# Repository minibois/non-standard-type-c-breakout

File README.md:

# mini-type-c-breakout
## Repository for a simple USB Type C breakout board, where the receptacle installs on the other side
 << [License](https://github.com/minibois/mini-non-standard-type-c-breakout/blob/master/LICENSE/LICENSE.txt) || [Bill of Materials](https://github.com/minibois/non-standard-type-c-breakout/blob/master/Documents/BOM.txt) || Schematic ([.pdf](https://github.com/minibois/mini-non-standard-type-c-breakout/blob/master/Documents/Schematic.pdf)) / ([.sch](https://github.com/minibois/mini-non-standard-type-c-breakout/blob/master/mini-type-c-breakout.sch)) || PCB ([.pdf](https://github.com/minibois/mini-non-standard-type-c-breakout/blob/master/Documents/PCB.pdf)) / ([.kicad_pcb](https://github.com/minibois/mini-non-standard-type-c-breakout/blob/master/mini-type-c-breakout.kicad_pcb)) >>

 This daughterboard allows for a USB 2.0 Type C by HRO receptacle to be installed on the opposite side of the Type C pins. This daughterboard was used in a keyboard repair project, so the receptacle could be installed on the keyboard cleanly.

### This PCB file and schematic is provided - as per CERN-OHL-S v2 section 6 - _without any warranty_ (implied or otherwise). https://ohwr.org/cern_ohl_s_v2.pdf

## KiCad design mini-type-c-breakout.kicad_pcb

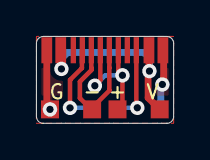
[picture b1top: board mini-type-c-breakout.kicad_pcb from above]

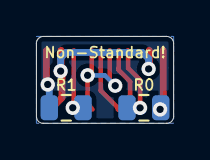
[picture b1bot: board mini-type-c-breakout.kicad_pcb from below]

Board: 2 copper layers, 7.6 x 4.8 mm, 7 parts (2 on the bottom side), 6 nets.

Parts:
+: Conn_01x01; TestPoint_Pad_1.0x1.0mm
-: Conn_01x01; TestPoint_Pad_1.0x1.0mm
G: Conn_01x01; TestPoint_Pad_1.0x1.0mm
J0: TYPE-C-31-M12_13_EDITED; HRO-TYPE-C-No-SHIELD
R0, R1: 5.1k; R_0805_2012Metric
V: Conn_01x01; TestPoint_Pad_1.0x1.0mm

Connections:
GND: G.1, J0.1, J0.12, R0.1, R1.1
unnamed: J0.4, R0.2
unnamed: J0.10, R1.2
USB_D+: +.1, J0.6, J0.8
USB_D-: -.1, J0.5, J0.7
VCC: J0.2, J0.11, V.1

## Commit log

2021-09-01 Project initialize
2021-09-01 Imported libraries, made schematic, started work on PCB.
2021-09-01 Started PCB
2021-09-02 v1.0a complete
2021-10-18 Many tweaks, additions, etc.
    Added licensing, tweaked PCB silkscreen, added logos to schematic, tweaked schematic layout, etc.
2021-10-18 Updated URL in schematic
2021-10-19 Added PCB and schematic PDF, updated schematic file
2021-10-19 Edited BOM and ReadMe link to it

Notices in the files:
mini-type-c-breakout.kicad_pcb:
This PCB file describes Open Hardware and is licensed under the CERN-OHL-S v2.
